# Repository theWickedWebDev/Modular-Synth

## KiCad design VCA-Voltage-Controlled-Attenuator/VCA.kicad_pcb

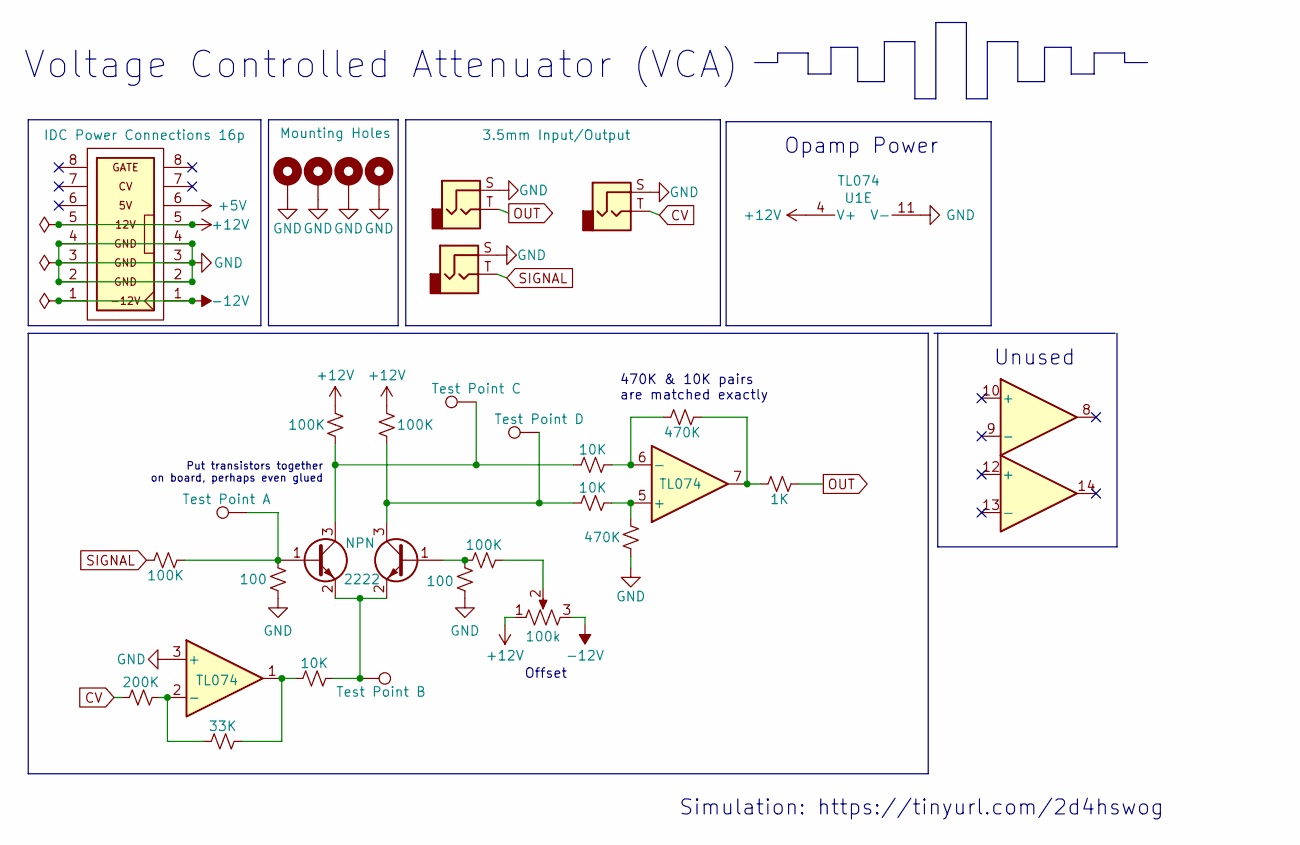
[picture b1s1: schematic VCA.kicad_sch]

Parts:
H1, H2, H3, H4: MountingHole_Pad; MountingHole_3mm_Pad_Via
J1, J2, J3: AudioJack2; ACJS-MV35-3S-audio-jack
Q1, Q2: 2N2222_smd-stephen; SOT-23
R1, R2, R3, R5, R6, R7, R10, R11, R13, R14: R_Small_US; R_0805_2012Metric
R4, R8, R9: R_Small_US; R_0805_2012Metric-10K
R12: R_Small_US; R_0805_2012Metric-1K-Gray
RV1: R_Potentiometer_US; Potentiometer_Omeg_PC16BU_Vertical
TP1, TP2, TP3, TP4: TestPoint; TestPoint_Pad_2.0x2.0mm
U1: TL074; SO-14_3.9x8.65mm_P1.27mm
U2: Eurorack_IDE_16P; IDC-Socket-Eurorack_16p_2.54mm

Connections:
+5V: U2.6 (5V)
+12V: R6.1, R7.1, RV1.1, U1.4 (V+), U2.5 (12V)
-12V: RV1.3, U2.1 (-12V)
CV: J3.T, R1.1
GND: H1.1, H2.1, H3.1, H4.1, J1.S, J2.S, J3.S, R5.1, R10.1, R13.1, U1.3 (+), U1.11 (V-), U2.2 (GND), U2.3 (GND), U2.4 (GND)
unnamed: Q1.1 (B), R3.1, R5.2, TP1.1
unnamed: Q1.2 (E), Q2.2 (E), R4.2, TP2.1
unnamed: Q1.3 (C), R6.2, R8.1, TP3.1
unnamed: Q2.1 (B), R13.2, R14.1
unnamed: Q2.3 (C), R7.2, R9.1, TP4.1
unnamed: R1.2, R2.1, U1.2 (-)
unnamed: R2.2, R4.1, U1.1
unnamed: R9.2, R10.2, U1.5 (+)
unnamed: R11.1, R12.2, U1.7
unnamed: R8.2, R11.2, U1.6 (-)
unnamed: R14.2, RV1.2
OUT: J1.T, R12.1
SIGNAL: J2.T, R3.2

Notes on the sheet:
Simulation: https://tinyurl.com/2d4hswog
470K & 10K pairs are matched exactly
Unused
Offset
Opamp Power
Voltage Controlled Attenuator (VCA)
Put transistors together on board, perhaps even glued

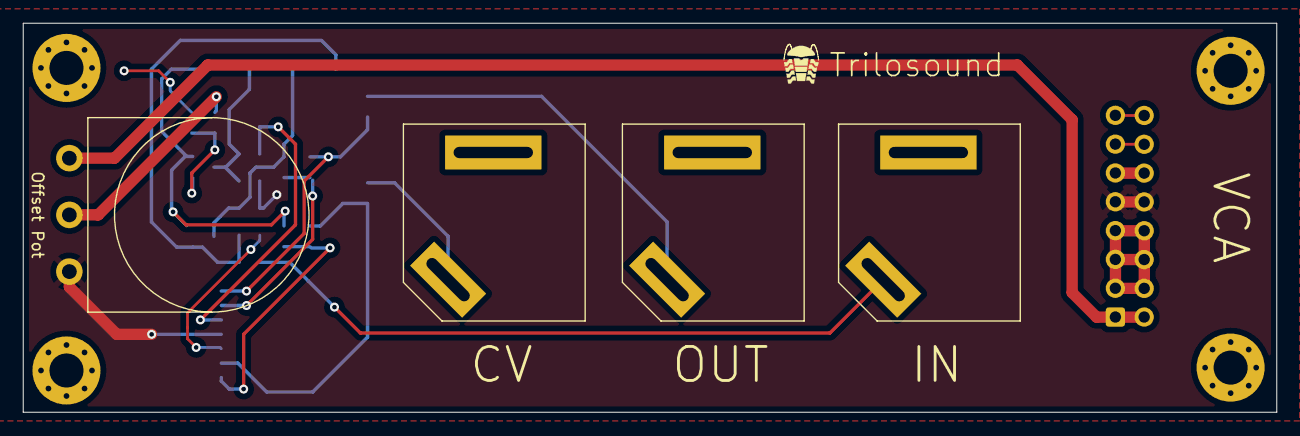
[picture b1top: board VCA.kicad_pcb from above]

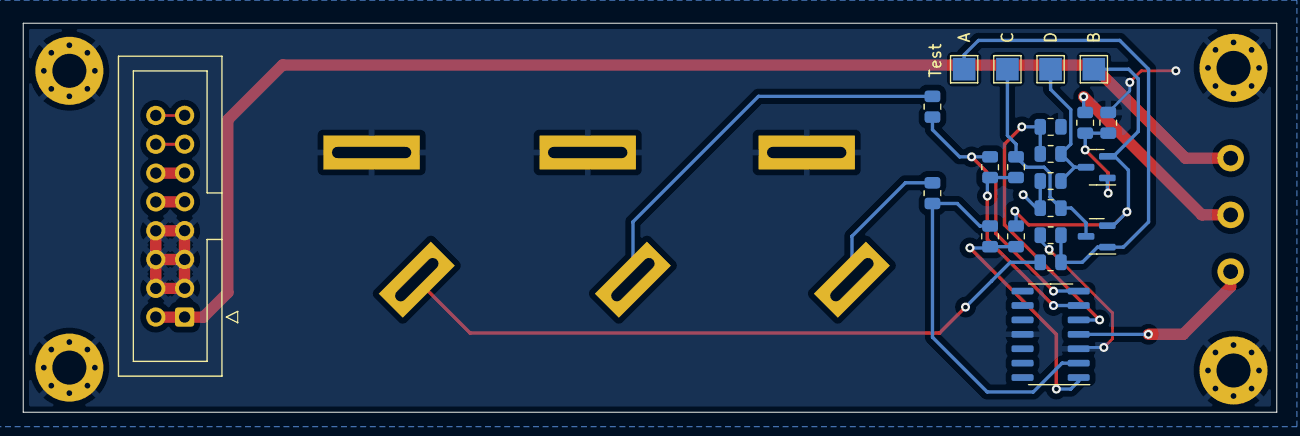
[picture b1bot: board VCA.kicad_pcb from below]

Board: 2 copper layers, 110.5 x 34.3 mm, 30 parts (22 on the bottom side), 17 nets.

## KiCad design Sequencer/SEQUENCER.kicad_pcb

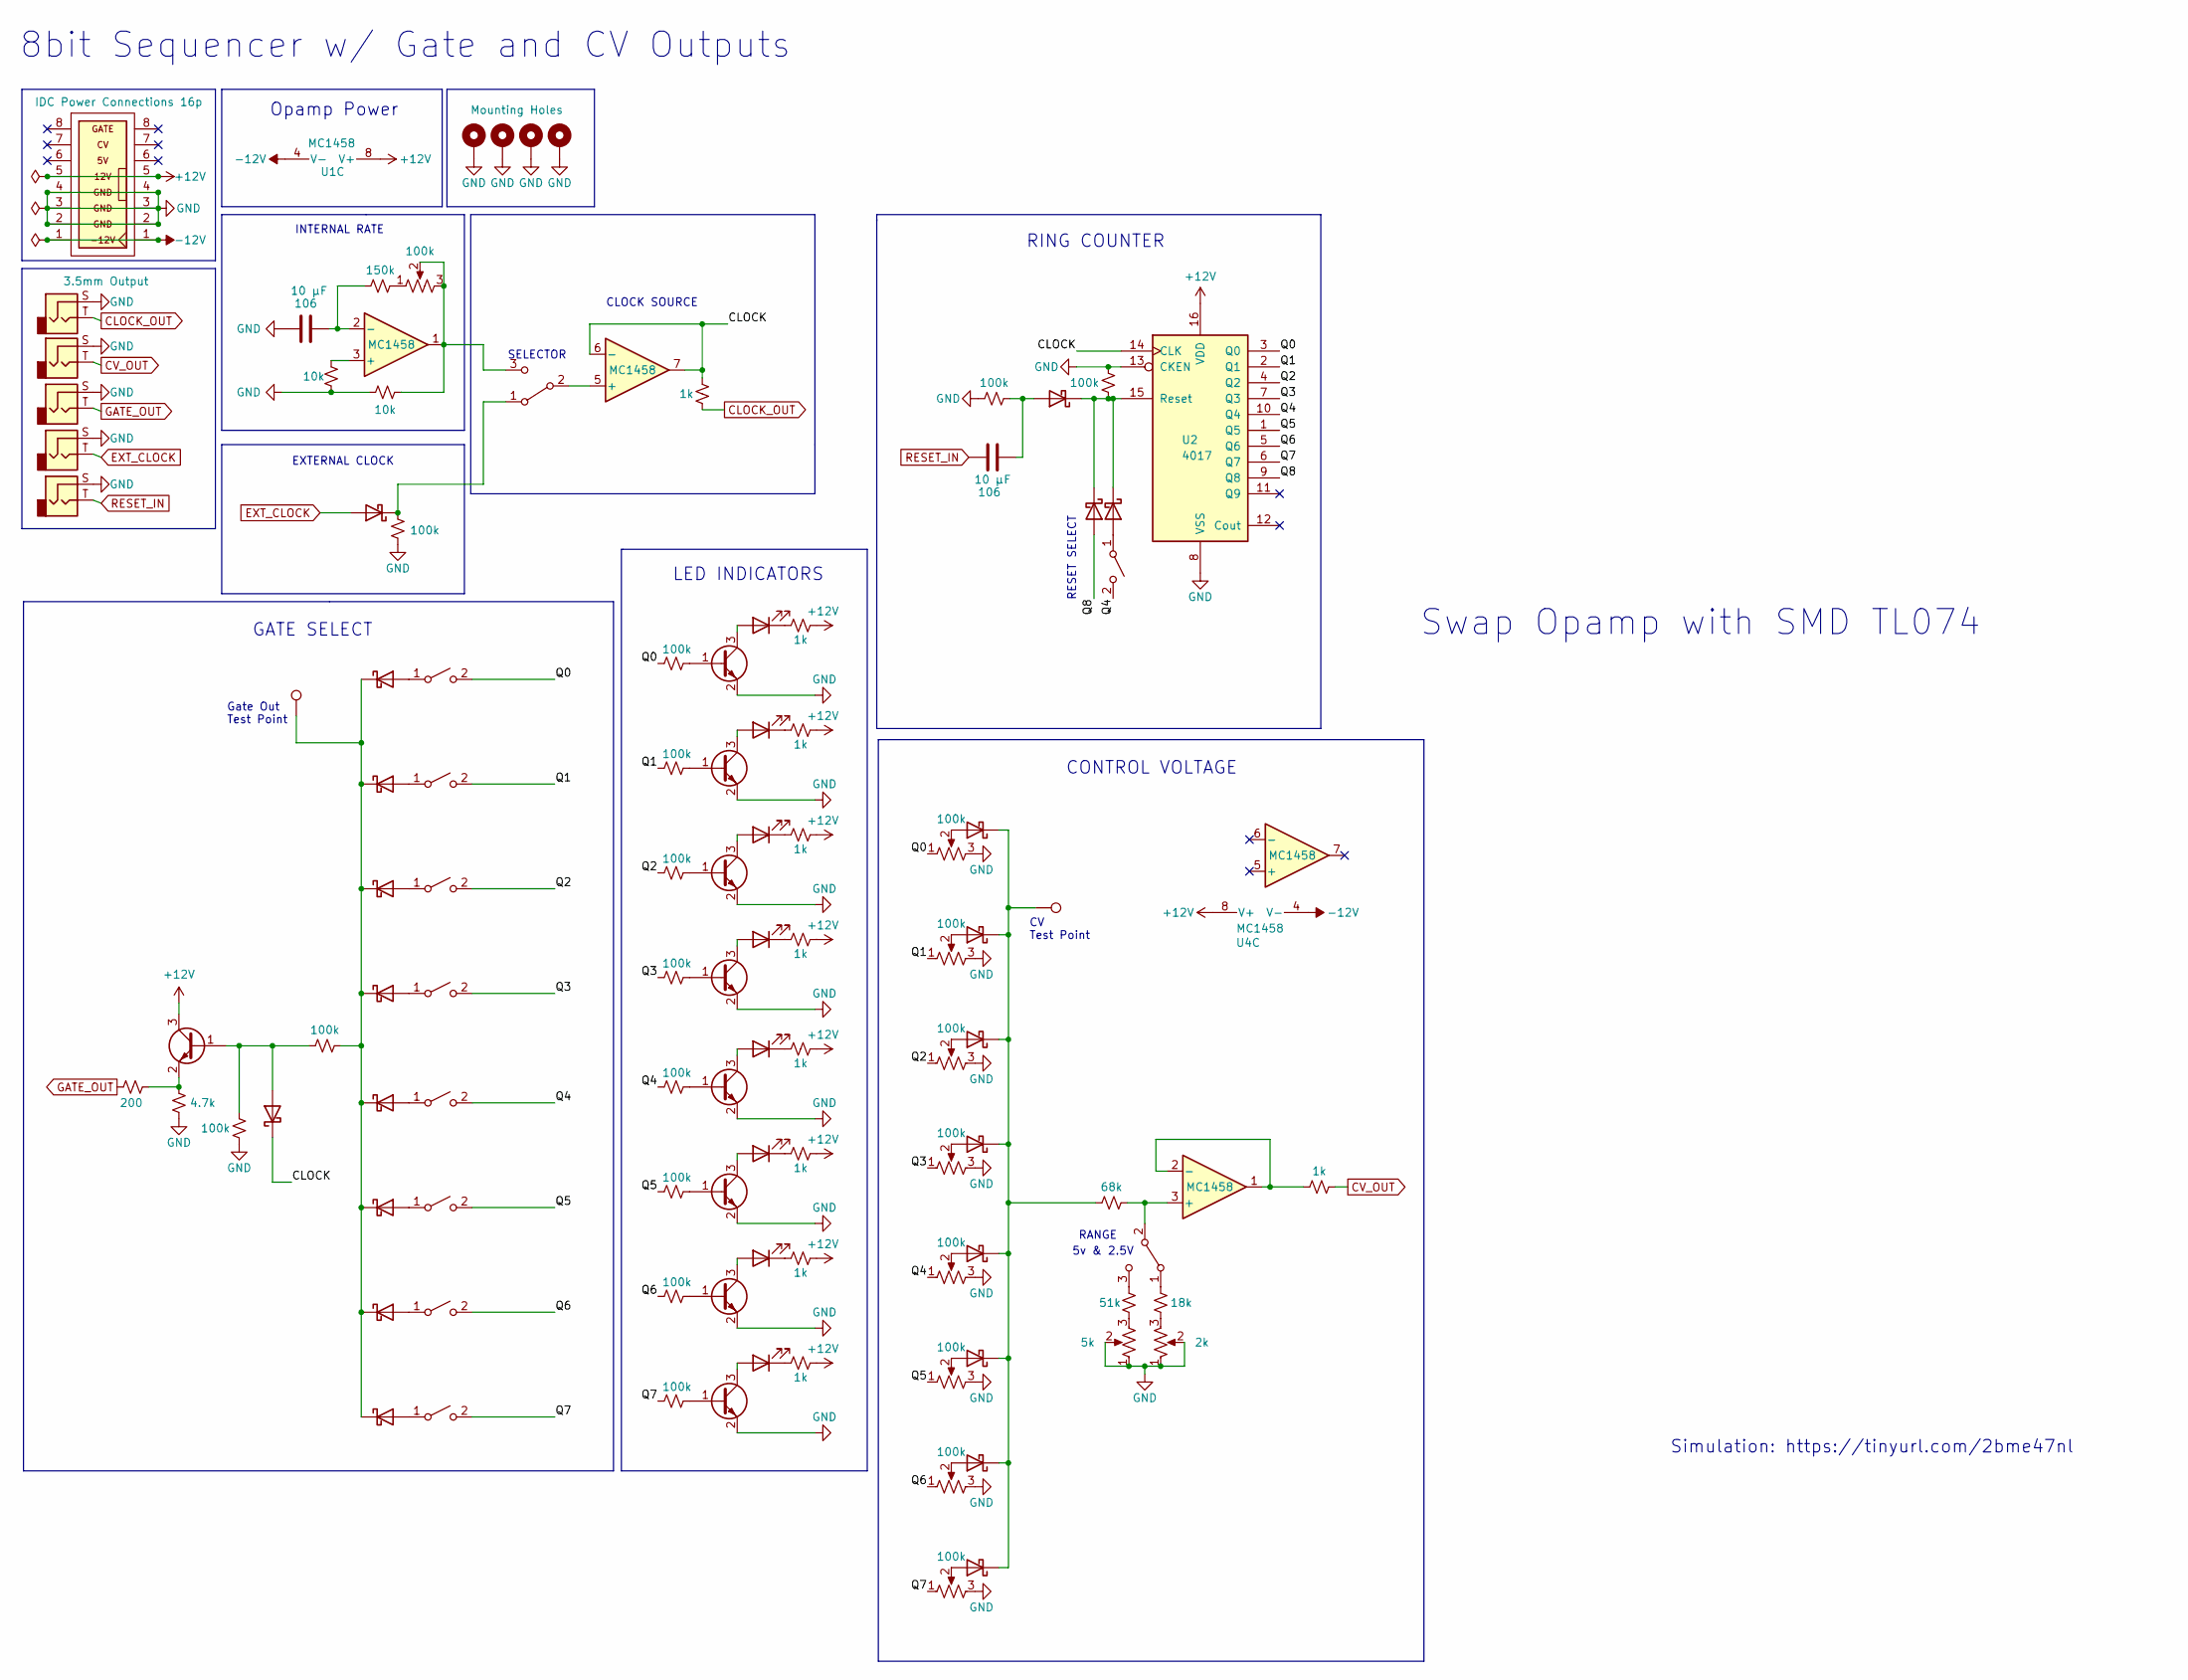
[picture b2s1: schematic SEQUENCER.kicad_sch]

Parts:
C1, C2: C; C_0805_2012Metric
D1, D2, D3, D12, D13, D14, D15, D16, D17, D18, D19, D20, D21, D22, D23, D24, D25, D26, D27, D28, D29: BAT54J; D_SOD-123
D4, D5, D6, D7, D8, D9, D10, D11: LED; LED_D5.0mm
H1, H2, H3, H4: MountingHole_Pad; MountingHole_3mm_Pad_Via
J1, J2, J3, J4, J5: AudioJack2; ACJS-MV35-3S-audio-jack
Q1, Q2, Q3, Q4, Q5, Q6, Q7, Q8, Q9: 2N2222_smd-stephen; SOT-23
R1, R3: R_Small_US; R_0805_2012Metric-10K
R2, R4, R5, R6, R7, R8, R9, R10, R11, R12, R13, R14, R15, R16, R17, R18, R19, R20, R21, R22, R23, R24, R25, R26, R27, R28, R29, R30: R_Small_US; R_0805_2012Metric
R33: R_Small_US; R_0805_2012Metric-1K-Gray
RV1, RV2, RV3, RV4, RV5, RV6, RV7, RV8, RV9: R_Potentiometer_US; Potentiometer_Omeg_PC16BU_Vertical
RV10, RV11: R_Potentiometer_US; Potentiometer_Bourns_3296W_Vertical
SW1, SW10: SW_DPDT_x2; SPDT-vertical-200MSP1T2B1M2QEH
SW2, SW3, SW4, SW5, SW6, SW7, SW8, SW9, SW11: SW_SPST; SPST-12mm-PushButton-Vertical
TP1, TP2: TestPoint; TestPoint_Pad_2.5x2.5mm
U1, U4: MC1458; SOIC-8_3.9x4.9mm_P1.27mm
U2: 4017; SO-16_3.9x9.9mm_P1.27mm
U3: Eurorack_IDE_16P; IDC-Socket-Eurorack_16p_2.54mm

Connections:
+12V: Q9.3 (C), R16.2, R17.2, R18.2, R19.2, R20.2, R21.2, R22.2, R23.2, U1.8 (V+), U2.16 (VDD), U3.5 (12V), U4.8 (V+)
-12V: U1.4 (V-), U3.1 (-12V), U4.4 (V-)
/CLOCK: D12.1 (K), R5.1, U1.6 (-), U1.7, U2.14 (CLK)
/Q0: R8.1, RV2.1, SW2.2 (B), U2.3 (Q0)
/Q1: R9.1, RV3.1, SW3.2 (B), U2.2 (Q1)
/Q2: R10.1, RV4.1, SW4.2 (B), U2.4 (Q2)
/Q3: R11.1, RV5.1, SW5.2 (B), U2.7 (Q3)
/Q4: R12.1, RV6.1, SW6.2 (B), SW11.2 (B), U2.10 (Q4)
/Q5: R13.1, RV7.1, SW7.2 (B), U2.1 (Q5)
/Q6: R14.1, RV8.1, SW8.2 (B), U2.5 (Q6)
/Q7: R15.1, RV9.1, SW9.2 (B), U2.6 (Q7)
/Q8: D3.2 (A), U2.9 (Q8)
CLOCK_OUT: J1.T, R5.2
CV_OUT: J2.T, R33.2
EXT_CLOCK: D1.2 (A), J4.T
GATE_OUT: J3.T, R24.2
GND: C1.1, H1.1, H2.1, H3.1, H4.1, J1.S, J2.S, J3.S, J4.S, J5.S, Q1.2 (E), Q2.2 (E), Q3.2 (E), Q4.2 (E), Q5.2 (E), Q6.2 (E), Q7.2 (E), Q8.2 (E), R1.1, R3.2, R4.2, R6.1, R7.1, R25.2, R26.1, RV2.3, RV3.3, RV4.3, RV5.3, RV6.3, RV7.3, RV8.3, RV9.3, RV10.1, RV10.2, RV11.1, RV11.2, U2.8 (VSS), U2.13 (CKEN), U3.2 (GND), U3.3 (GND), U3.4 (GND)
unnamed: C1.2, R2.2, U1.2 (-)
unnamed: C2.2, D2.2 (A), R6.2
unnamed: D1.1 (K), R4.1, SW1.1 (A)
unnamed: D2.1 (K), D3.1 (K), D29.1 (K), R7.2, U2.15 (Reset)
unnamed: D4.1 (K), R16.1
unnamed: D4.2 (A), Q1.3 (C)
unnamed: D5.1 (K), R17.1
unnamed: D5.2 (A), Q2.3 (C)
unnamed: D6.1 (K), R18.1
unnamed: D6.2 (A), Q3.3 (C)
unnamed: D7.1 (K), R19.1
unnamed: D7.2 (A), Q4.3 (C)
unnamed: D8.1 (K), R20.1
unnamed: D8.2 (A), Q5.3 (C)
unnamed: D9.1 (K), R21.1
unnamed: D9.2 (A), Q6.3 (C)
unnamed: D10.1 (K), R22.1
unnamed: D10.2 (A), Q7.3 (C)
unnamed: D11.1 (K), R23.1
unnamed: D11.2 (A), Q8.3 (C)
unnamed: D12.2 (A), Q9.1 (B), R26.2, R27.1
unnamed: D13.1 (K), D14.1 (K), D15.1 (K), D16.1 (K), D17.1 (K), D18.1 (K), D19.1 (K), D20.1 (K), R27.2, TP2.1
unnamed: D13.2 (A), SW2.1 (A)
unnamed: D14.2 (A), SW3.1 (A)
unnamed: D15.2 (A), SW4.1 (A)
unnamed: D16.2 (A), SW5.1 (A)
unnamed: D17.2 (A), SW6.1 (A)
unnamed: D18.2 (A), SW7.1 (A)
unnamed: D19.2 (A), SW8.1 (A)
unnamed: D20.2 (A), SW9.1 (A)
unnamed: D21.1 (K), D22.1 (K), D23.1 (K), D24.1 (K), D25.1 (K), D26.1 (K), D27.1 (K), D28.1 (K), R28.1, TP1.1
unnamed: D21.2 (A), RV2.2
unnamed: D22.2 (A), RV3.2
unnamed: D23.2 (A), RV4.2
unnamed: D24.2 (A), RV5.2
unnamed: D25.2 (A), RV6.2
unnamed: D26.2 (A), RV7.2
unnamed: D27.2 (A), RV8.2
unnamed: D28.2 (A), RV9.2
unnamed: D29.2 (A), SW11.1 (A)
unnamed: Q1.1 (B), R8.2
unnamed: Q2.1 (B), R9.2
unnamed: Q3.1 (B), R10.2
unnamed: Q4.1 (B), R11.2
unnamed: Q5.1 (B), R12.2
unnamed: Q6.1 (B), R13.2
unnamed: Q7.1 (B), R14.2
unnamed: Q8.1 (B), R15.2
unnamed: Q9.2 (E), R24.1, R25.1
unnamed: R1.2, U1.3 (+)
unnamed: R2.1, RV1.1
unnamed: R3.1, RV1.2, RV1.3, SW1.3 (C), U1.1
unnamed: R28.2, SW10.2 (B), U4.3 (+)
unnamed: R29.1, RV10.3
unnamed: R29.2, SW10.3 (C)
unnamed: R30.1, RV11.3
unnamed: R30.2, SW10.1 (A)
unnamed: R33.1, U4.1, U4.2 (-)
unnamed: SW1.2 (B), U1.5 (+)
RESET_IN: C2.1, J5.T

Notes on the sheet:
8bit Sequencer w/ Gate and CV Outputs
Opamp Power
GATE SELECT
EXTERNAL CLOCK
Swap Opamp with SMD TL074
5v & 2.5V
CLOCK SOURCE
INTERNAL RATE
CV Test Point
RING COUNTER
LED INDICATORS
RESET SELECT
Gate Out Test Point
CONTROL VOLTAGE
RANGE
Simulation: https://tinyurl.com/2bme47nl
SELECTOR

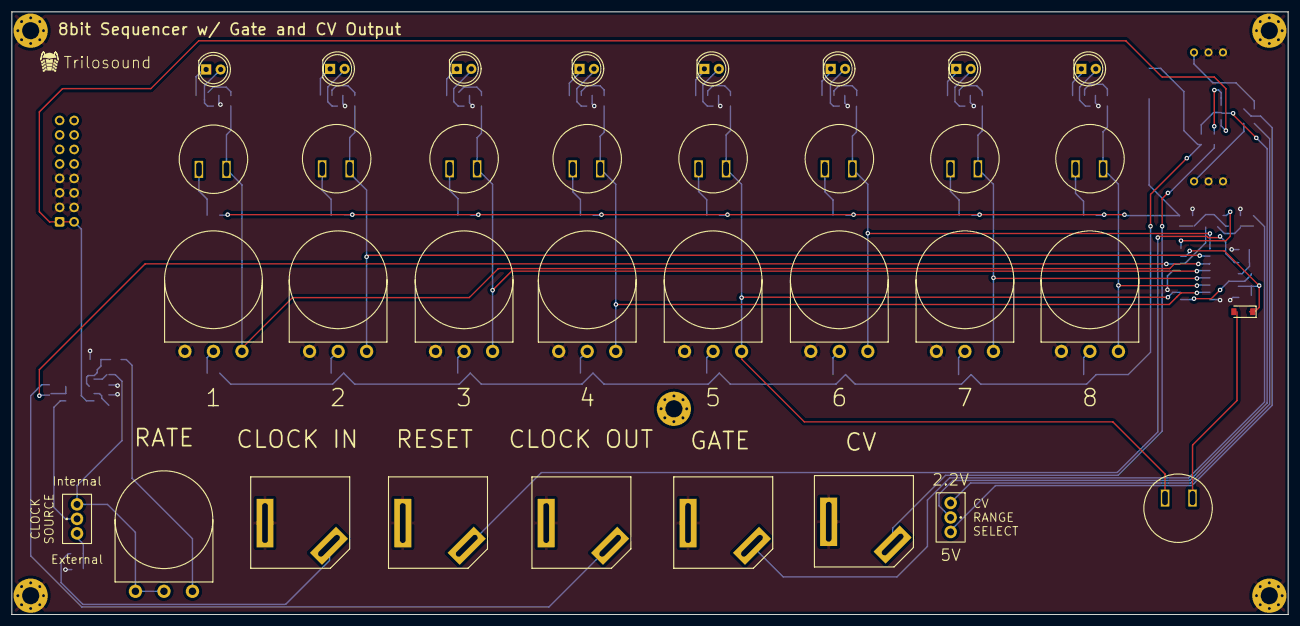
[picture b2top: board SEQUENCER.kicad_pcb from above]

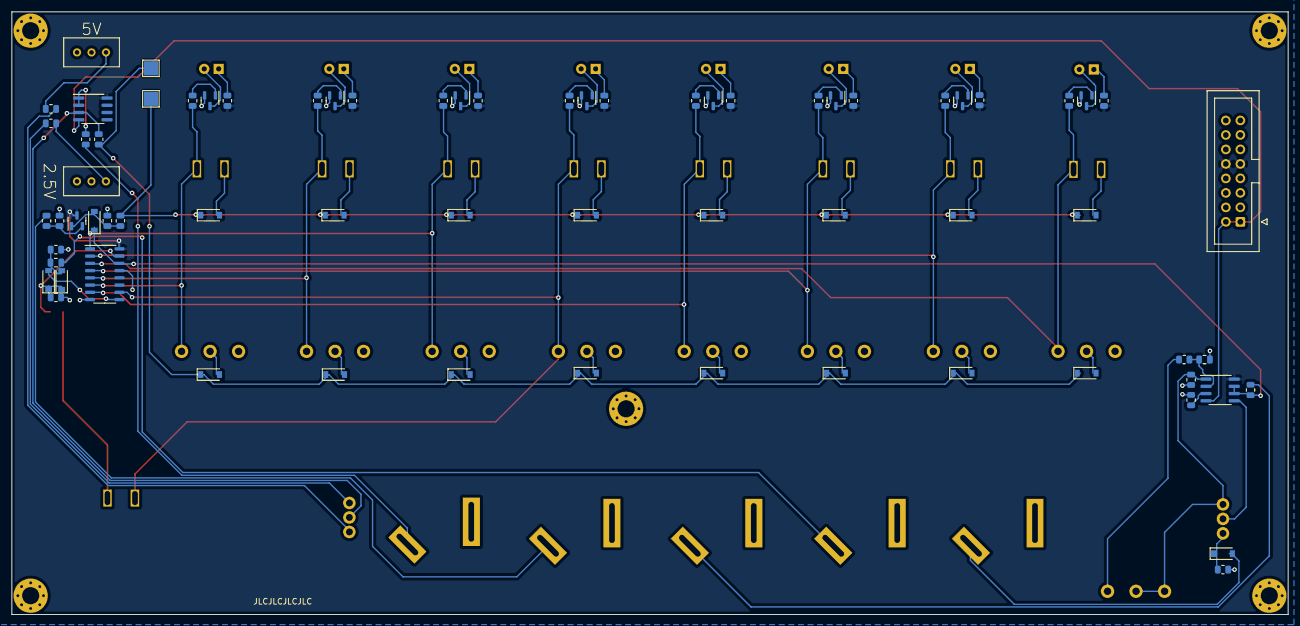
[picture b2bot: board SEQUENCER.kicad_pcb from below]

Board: 2 copper layers, 223.8 x 105.7 mm, 108 parts (70 on the bottom side), 77 nets.

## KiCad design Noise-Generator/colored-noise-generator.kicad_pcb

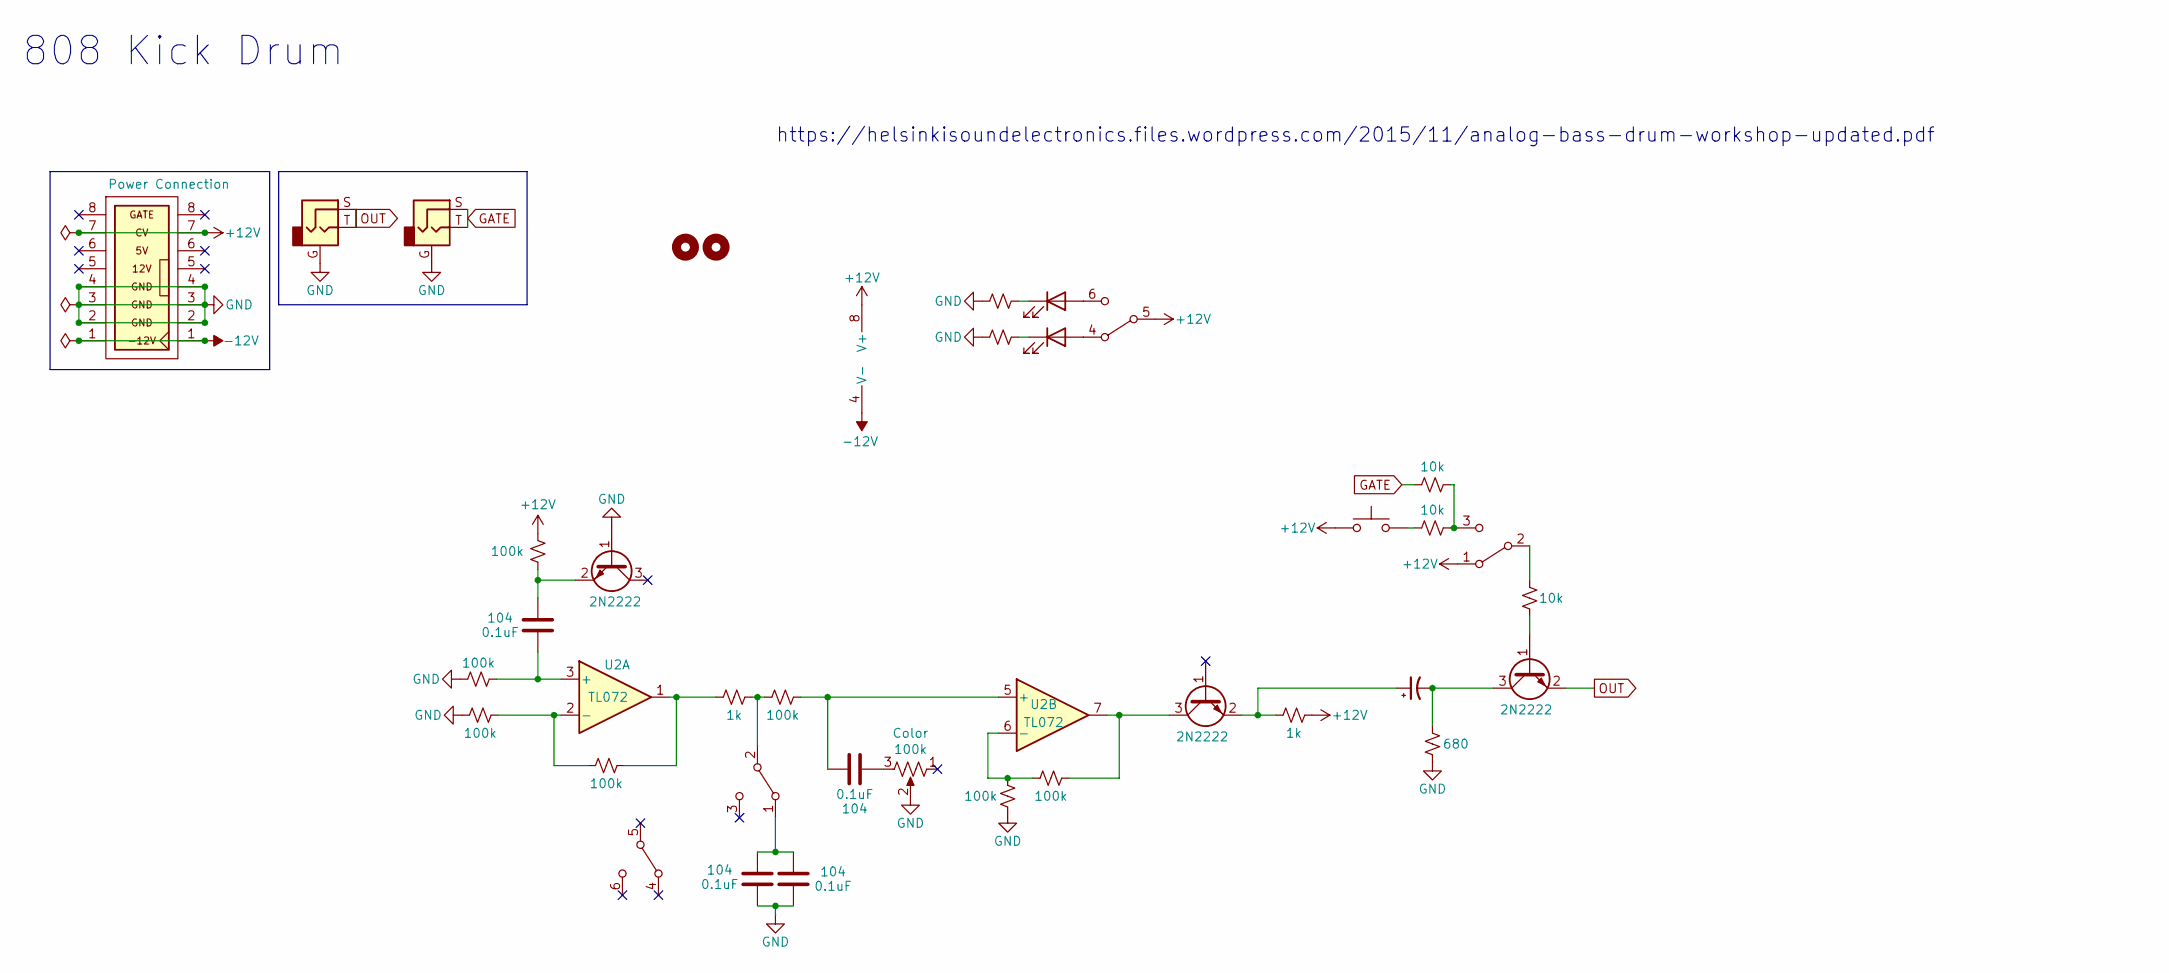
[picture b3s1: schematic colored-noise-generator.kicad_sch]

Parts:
C1, C2, C3, C4: C; C_0805_2012Metric
C5: C_Polarized_Small_US; CP_Elec_8x10.5
D1, D2: LED; LED_D3.0mm
H1, H2: MountingHole; 3.2mm-mounting-hole-eurorack
J1, J2: AudioJack2_Ground; 3.5mm-mono-jack-eurorack-2
Q1, Q2, Q3: 2N2222; 2222-SMD-SOT23-with-label
R1, R2, R3, R4, R5, R6, R7, R8, R9, R10, R11, R12, R13, R14, R15: R_Small_US; R_0805_2012Metric
RV1: R_Potentiometer_US; alpha-9mm-potentiometer
SW1, SW2: SW_DPDT_x2; DPDT-LatchingSwitch-THT
SW3: SW_Push; SW_PUSH_6mm
U1: Eurorack_IDE_16P; IDC-Socket-Eurorack_16p_2.54mm
U2: TL072; SO-8_3.9x4.9mm_P1.27mm

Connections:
+12V: R3.1, R9.1, SW2.1 (A), SW2.5 (B), SW3.1, U1.7 (CV), U2.8 (V+)
-12V: U1.1 (-12V), U2.4 (V-)
GATE: J2.S, J2.T, R12.1
GND: C2.2, C3.2, J1.G, J2.G, Q1.1 (B), R1.2, R2.2, R7.2, R10.1, R11.1, R14.2, RV1.2, U1.2 (GND), U1.3 (GND), U1.4 (GND)
unnamed: C1.1, Q1.2 (E), R3.2
unnamed: C1.2, R1.1, U2.3 (+)
unnamed: C2.1, C3.1, SW1.1 (A)
unnamed: C4.1, R6.1, U2.5 (+)
unnamed: C4.2, RV1.3
unnamed: C5.1, Q2.2 (E), R9.2
unnamed: C5.2, Q3.3 (C), R14.1
unnamed: D1.1 (K), R10.2
unnamed: D1.2 (A), SW2.6 (C)
unnamed: D2.1 (K), R11.2
unnamed: D2.2 (A), SW2.4 (A)
unnamed: Q2.3 (C), R8.1, U2.7
unnamed: Q3.1 (B), R15.1
unnamed: R2.1, R4.2, U2.2 (-)
unnamed: R4.1, R5.2, U2.1
unnamed: R5.1, R6.2, SW1.2 (B)
unnamed: R7.1, R8.2, U2.6 (-)
unnamed: R12.2, R13.2, SW2.3 (C)
unnamed: R13.1, SW3.2
unnamed: R15.2, SW2.2 (B)
OUT: J1.S, J1.T, Q3.2 (E)

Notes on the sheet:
https://helsinkisoundelectronics.files.wordpress.com/2015/11/analog-bass-drum-workshop-updated.pdf
808 Kick Drum

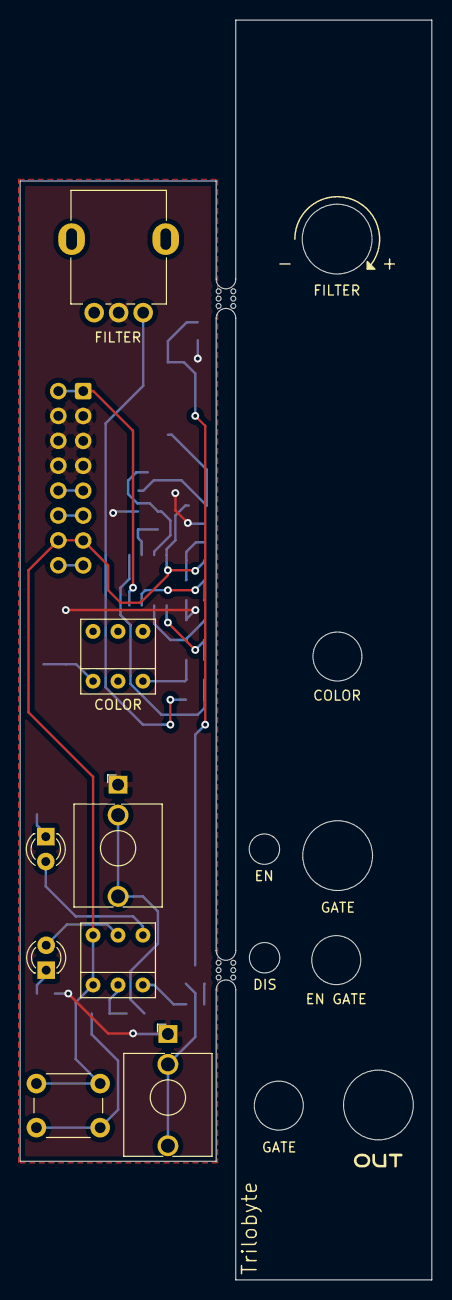
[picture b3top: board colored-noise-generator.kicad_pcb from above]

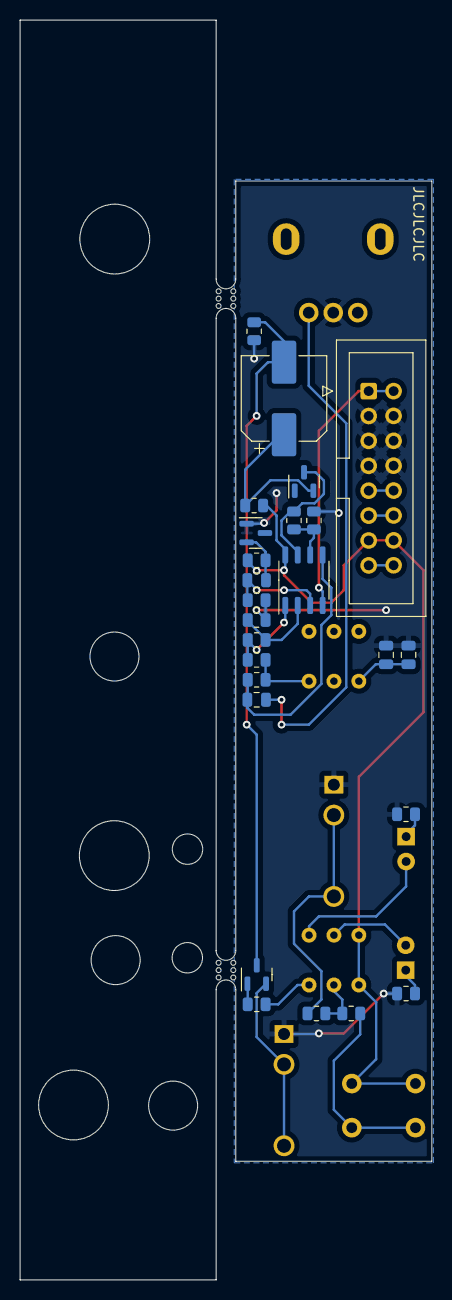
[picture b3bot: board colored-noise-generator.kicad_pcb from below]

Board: 2 copper layers, 42.0 x 128.5 mm, 37 parts (25 on the bottom side), 25 nets.

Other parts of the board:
mouse-bite-2mm-slot, mouse-bite-2mm-slot#2: VAL**; mouse-bite-2mm-slot

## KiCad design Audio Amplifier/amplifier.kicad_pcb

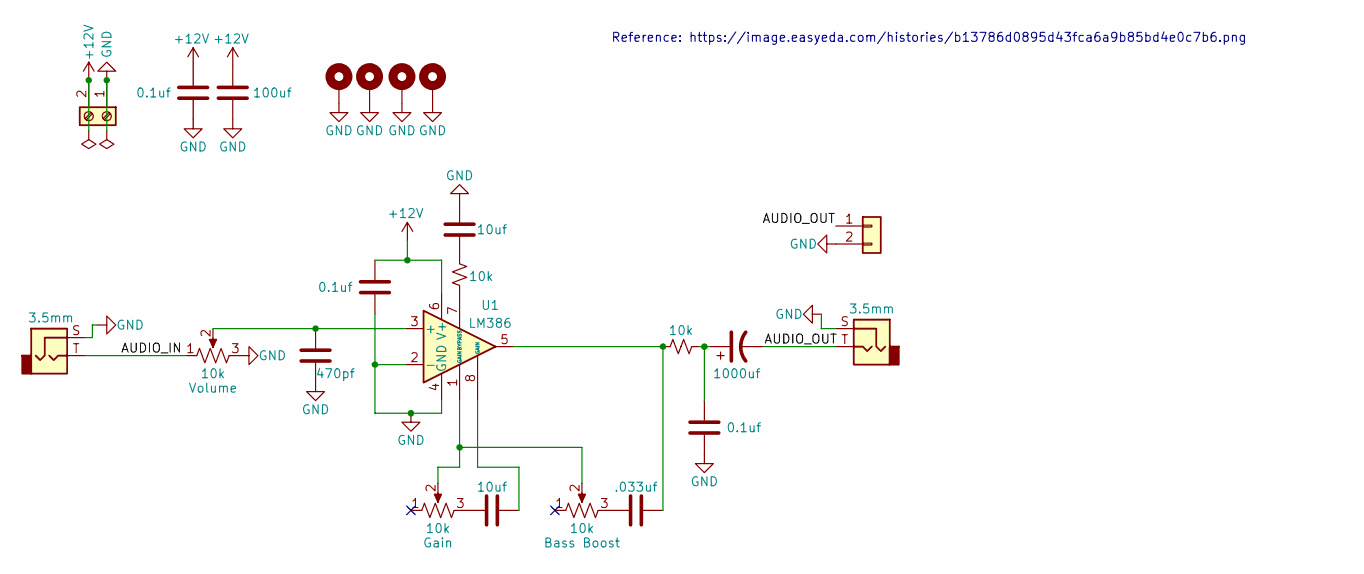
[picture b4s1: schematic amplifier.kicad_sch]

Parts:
C1, C2, C3, C4, C5, C6, C7, C8: C; C_0805_2012Metric
C9: C_Polarized_US; CP_Elec_10x10.5
H1, H2, H3, H4: MountingHole_Pad; MountingHole_3mm_Pad_Via
J1, J3: AudioJack2; ACJS-MV35-3S-audio-jack
J2: Screw_Terminal_01x02; ScrewTerminal_1x2-Connectable
J4: Conn_01x02; PinHeader_1x02_P2.54mm_Horizontal
R1, R2: R_Small_US; R_0805_2012Metric
RV1, RV2, RV3: R_Potentiometer_US; Potentiometer_Omeg_PC16BU_Vertical
U1: LM386; DIP-8_W7.62mm

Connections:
+12V: C1.2, C2.2, C4.2, J2.2, U1.6 (V+)
/AUDIO_IN: J1.T, RV1.1
/AUDIO_OUT: C9.2, J3.T, J4.1
GND: C1.1, C2.1, C3.1, C4.1, C5.2, C8.2, H1.1, H2.1, H3.1, H4.1, J1.S, J2.1, J3.S, J4.2, RV1.3, U1.2 (-), U1.4 (GND)
unnamed: C3.2, RV1.2, U1.3 (+)
unnamed: C5.1, R1.2
unnamed: C6.1, U1.8 (GAIN)
unnamed: C6.2, RV2.3
unnamed: C7.1, R2.2, U1.5
unnamed: C7.2, RV3.3
unnamed: C8.1, C9.1, R2.1
unnamed: R1.1, U1.7 (BYPASS)
unnamed: RV2.2, RV3.2, U1.1 (GAIN)

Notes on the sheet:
Reference: https://image.easyeda.com/histories/b13786d0895d43fca6a9b85bd4e0c7b6.png

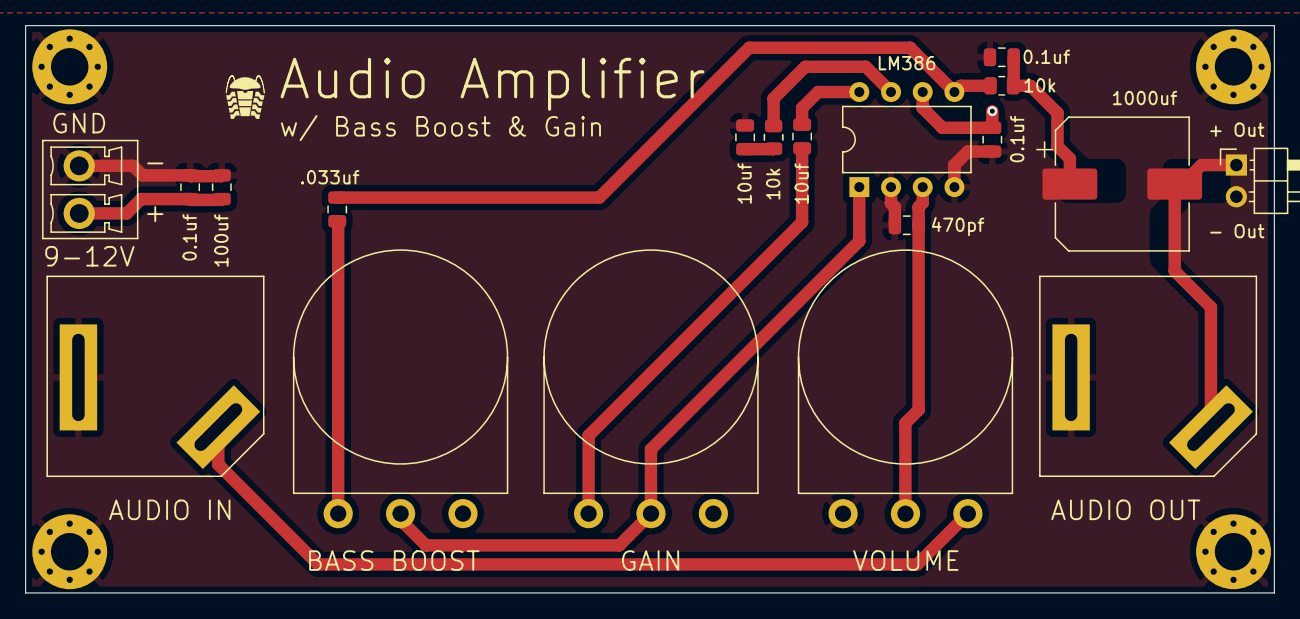
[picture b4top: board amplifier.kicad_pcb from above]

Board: 2 copper layers, 100.1 x 45.5 mm, 23 parts (0 on the bottom side), 13 nets.

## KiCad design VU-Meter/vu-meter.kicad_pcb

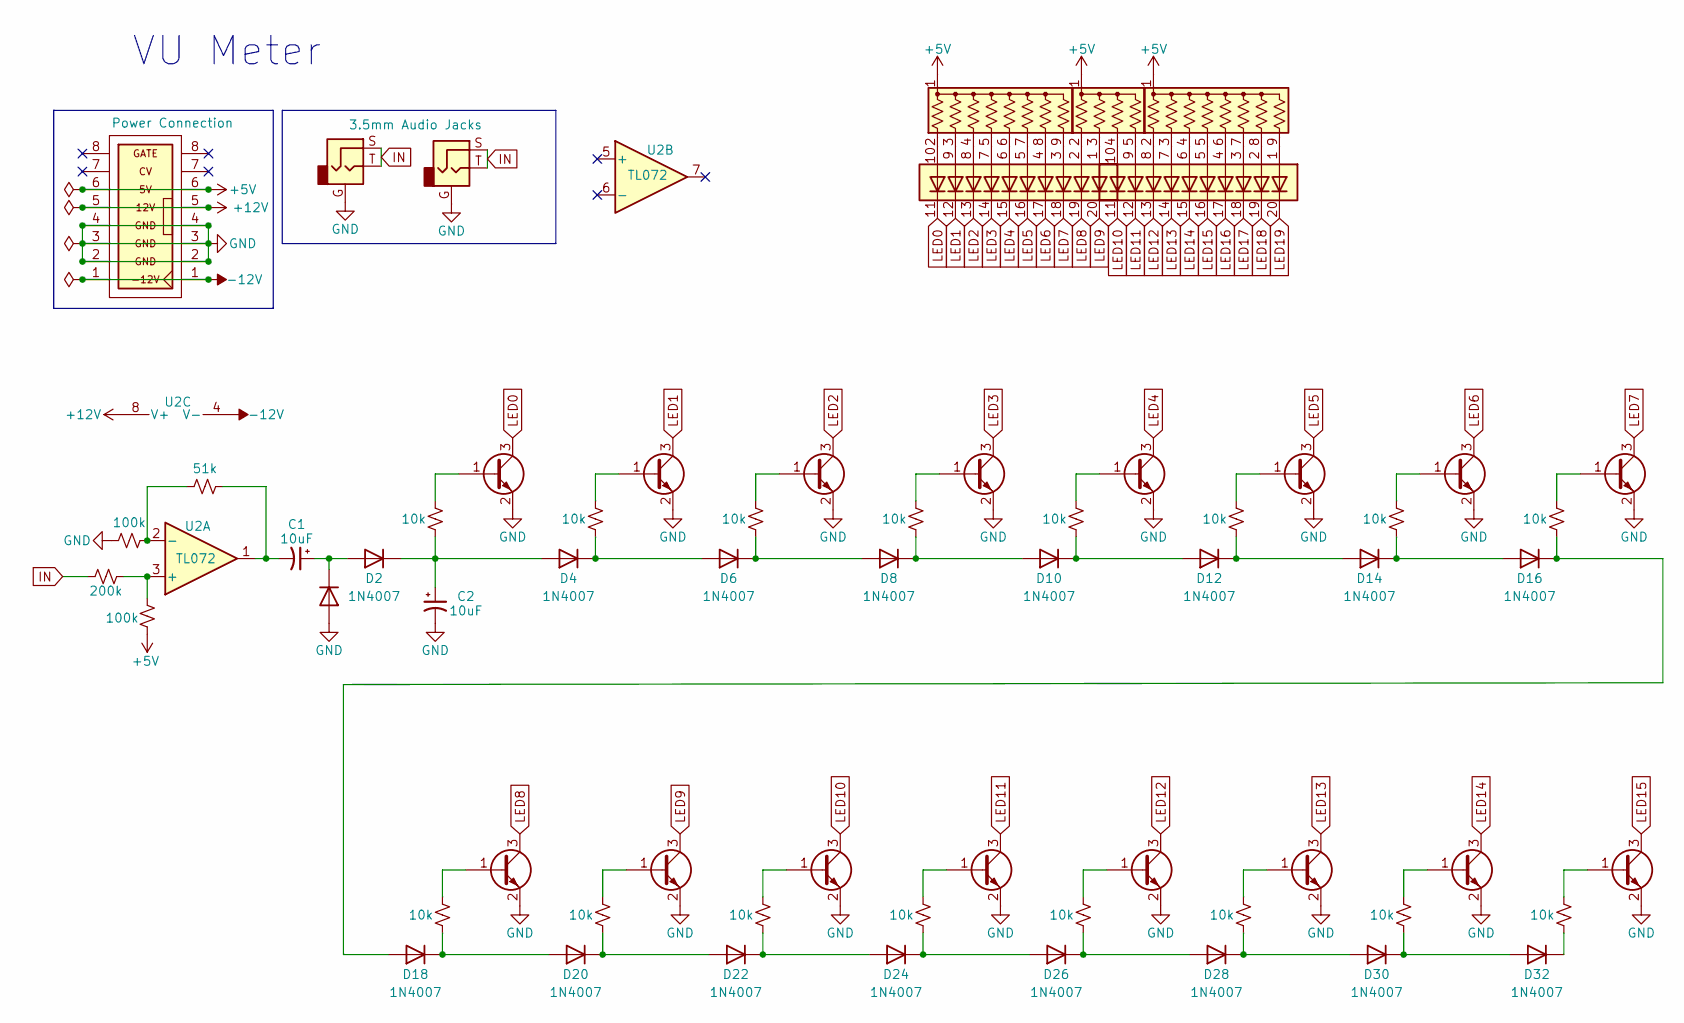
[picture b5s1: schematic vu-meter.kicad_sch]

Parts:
BAR1, BAR2: HDSP-4830_2; HDSP-4830
C1, C2: C_Polarized_Small_US; CP_Elec_4x5.4
D1, D2, D4, D6, D8, D10, D12, D14, D16, D18, D20, D22, D24, D26, D28, D30, D32: 1N4007; D_SOD-123
J1, J2: AudioJack2_Ground; 3.5mm-mono-jack-eurorack-2
Q1, Q2, Q3, Q4, Q5, Q6, Q7, Q8, Q9, Q10, Q11, Q12, Q13, Q14, Q15, Q17: 2N2222_smd-stephen; 2222-SMD-SOT23-with-label
R1, R2, R3, R4, R6, R8, R10, R12, R13, R14, R16, R18, R20, R22, R24, R26, R28, R30, R32, R34: R_Small_US; R_0805_2012Metric
RN1, RN3: R_Network08_US; R_Array_SIP9
RN2: R_Network04_US; R_Array_SIP5
U1: Eurorack_IDE_16P; IDC-Socket-Eurorack_16p_2.54mm
U2: TL072; SOIC-8_3.9x4.9mm_P1.27mm

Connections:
+5V: R13.2, RN1.1 (common), RN2.1 (common), RN3.1 (common), U1.6 (5V)
+12V: U1.5 (12V), U2.8 (V+)
-12V: U1.1 (-12V), U2.4 (V-)
GND: C2.2, D1.2 (A), J1.G, J2.G, Q1.2 (E), Q2.2 (E), Q3.2 (E), Q4.2 (E), Q5.2 (E), Q6.2 (E), Q7.2 (E), Q8.2 (E), Q9.2 (E), Q10.2 (E), Q11.2 (E), Q12.2 (E), Q13.2 (E), Q14.2 (E), Q15.2 (E), Q17.2 (E), R1.2, U1.2 (GND), U1.3 (GND), U1.4 (GND)
IN: J1.S, J1.T, J2.S, J2.T, R2.1
LED0: BAR1.11 (K), Q3.3 (C)
LED1: BAR1.12 (K), Q5.3 (C)
LED2: BAR1.13 (K), Q7.3 (C)
LED3: BAR1.14 (K), Q9.3 (C)
LED4: BAR1.15 (K), Q11.3 (C)
LED5: BAR1.16 (K), Q13.3 (C)
LED6: BAR1.17 (K), Q15.3 (C)
LED7: BAR1.18 (K), Q17.3 (C)
LED8: BAR1.19 (K), Q1.3 (C)
LED9: BAR1.20 (K), Q2.3 (C)
LED10: BAR2.11 (K), Q4.3 (C)
LED11: BAR2.12 (K), Q6.3 (C)
LED12: BAR2.13 (K), Q8.3 (C)
LED13: BAR2.14 (K), Q10.3 (C)
LED14: BAR2.15 (K), Q12.3 (C)
LED15: BAR2.16 (K), Q14.3 (C)
unnamed: BAR1.1 (A), RN2.3 (R2)
unnamed: BAR1.2 (A), RN2.2 (R1)
unnamed: BAR1.3 (A), RN1.9 (R8)
unnamed: BAR1.4 (A), RN1.8 (R7)
unnamed: BAR1.5 (A), RN1.7 (R6)
unnamed: BAR1.6 (A), RN1.6 (R5)
unnamed: BAR1.7 (A), RN1.5 (R4)
unnamed: BAR1.8 (A), RN1.4 (R3)
unnamed: BAR1.9 (A), RN1.3 (R2)
unnamed: BAR1.10 (A), RN1.2 (R1)
unnamed: BAR2.1 (A), RN3.9 (R8)
unnamed: BAR2.2 (A), RN3.8 (R7)
unnamed: BAR2.3 (A), RN3.7 (R6)
unnamed: BAR2.4 (A), RN3.6 (R5)
unnamed: BAR2.5 (A), RN3.5 (R4)
unnamed: BAR2.6 (A), RN3.4 (R3)
unnamed: BAR2.7 (A), RN3.3 (R2)
unnamed: BAR2.8 (A), RN3.2 (R1)
unnamed: BAR2.9 (A), RN2.5 (R4)
unnamed: BAR2.10 (A), RN2.4 (R3)
unnamed: C1.1, D1.1 (K), D2.2 (A)
unnamed: C1.2, R3.1, U2.1
unnamed: C2.1, D2.1 (K), D4.2 (A), R4.2
unnamed: D4.1 (K), D6.2 (A), R6.2
unnamed: D6.1 (K), D8.2 (A), R8.2
unnamed: D10.1 (K), D12.2 (A), R12.2
unnamed: D8.1 (K), D10.2 (A), R10.2
unnamed: D12.1 (K), D14.2 (A), R14.2
unnamed: D14.1 (K), D16.2 (A), R16.2
unnamed: D16.1 (K), D18.2 (A), R18.2
unnamed: D18.1 (K), D20.2 (A), R20.2
unnamed: D20.1 (K), D22.2 (A), R22.2
unnamed: D22.1 (K), D24.2 (A), R24.2
unnamed: D24.1 (K), D26.2 (A), R26.2
unnamed: D26.1 (K), D28.2 (A), R28.2
unnamed: D28.1 (K), D30.2 (A), R30.2
unnamed: D30.1 (K), D32.2 (A), R32.2
unnamed 62: D32.1 (K), R34.2; also elsewhere on the board
unnamed: R1.1, R3.2, U2.2 (-)
unnamed: R2.2, R13.1, U2.3 (+)
unnamed: Q3.1 (B), R4.1
unnamed: Q5.1 (B), R6.1
unnamed: Q7.1 (B), R8.1
unnamed: Q9.1 (B), R10.1
unnamed: Q11.1 (B), R12.1
unnamed: Q13.1 (B), R14.1
unnamed: Q15.1 (B), R16.1
unnamed: Q17.1 (B), R18.1
unnamed: Q1.1 (B), R20.1
unnamed: Q2.1 (B), R22.1
unnamed: Q4.1 (B), R24.1
unnamed: Q6.1 (B), R26.1
unnamed: Q8.1 (B), R28.1
unnamed: Q10.1 (B), R30.1
unnamed: Q12.1 (B), R32.1
unnamed: Q14.1 (B), R34.1

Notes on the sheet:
VU Meter

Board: 2 copper layers, 63 parts (61 on the bottom side), 44 nets, no tracks yet.

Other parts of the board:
D3, D5, D7, D9: 1N4007; D_SOD-123

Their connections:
unnamed: D3.1 (K), D5.2 (A)
unnamed: D5.1 (K), D7.2 (A)
unnamed: D7.1 (K), D9.2 (A)
unnamed 62: D3.2 (A); also elsewhere on the board
